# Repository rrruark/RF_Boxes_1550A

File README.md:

<p>Design files for a few electronics projects.</p>

<ul>
  <li>LNA Box: http://robruark.com/projects/RF/LNA/general_purpose_lna/general_lna.html</li>
  <li>Filter box: http://robruark.com/projects/RF/Filters/ham_filter_box/filter_box.html</li>
</ul>

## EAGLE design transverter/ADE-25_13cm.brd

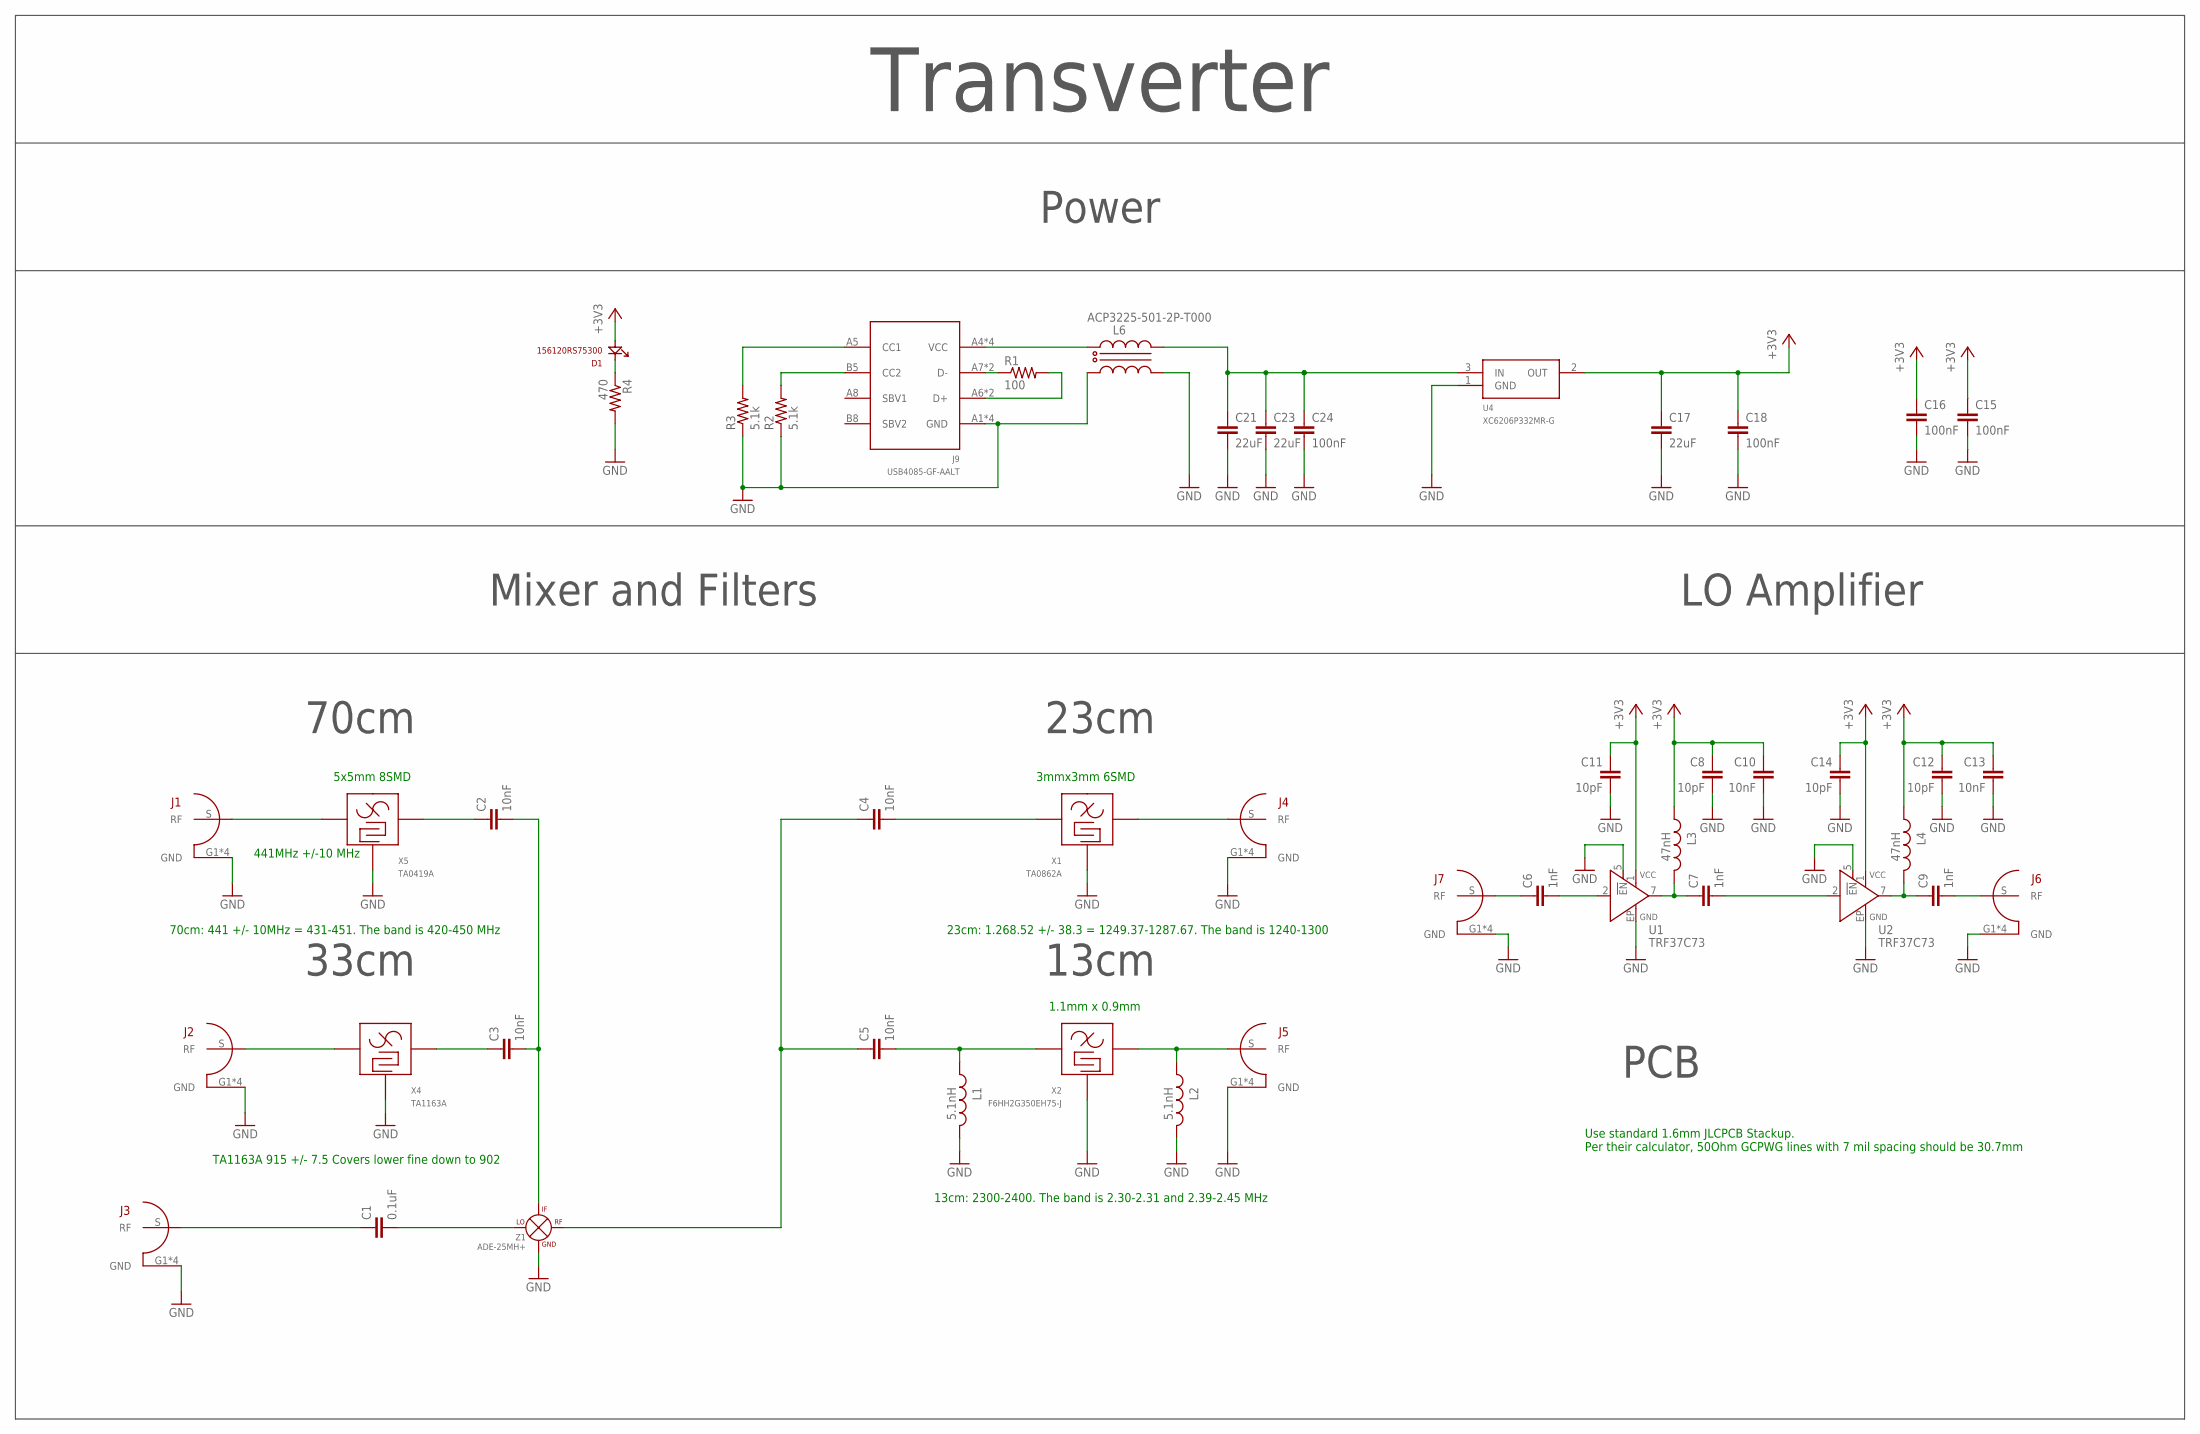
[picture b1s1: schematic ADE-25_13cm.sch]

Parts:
C1: 0.1uF; 0603
C2, C3, C4, C5: 10nF; 0603
C6, C7, C9: 1nF; 0603
C8, C11, C12, C14: 10pF; 0402_INDUCTOR
C10, C13: 10nF; 0402_INDUCTOR
C15, C16, C18, C24: 100nF; 0603
C17, C21, C23: 22uF; C1206
D1: 156120RS75300; 1206_REV
J1, J2, J3, J4, J5, J6, J7: 0733910070; CONREVSMA008-G
J9: USB4085-GF-AALT; USBC2
L1, L2: 5.1nH; 0402_INDUCTOR
L3, L4: 47nH; 0402_INDUCTOR
L6: ACP3225-501-2P-T000; 3225
R1: 100; 0603
R2, R3: 5.1k; 0603
R4: 470; 0603
U1, U2: TRF37C73; 8WSON2X2
U4: XC6206P332MR-G; SOT23-3_CENTERED
X1: TA0862A
X2: F6HH2G350EH75-J; EH75
X4: TA1163A; TA0862A
X5: TA0419A; TAO419
Z1: ADE-25MH+; CD

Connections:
1I: C4.2, X1.B
1O: J4.S (RF), X1.E
2I: C5.2, L1.P$1, X2.1
2O: J5.S (RF), L2.P$1, X2.4
70BI: C3.1, X4.B
70BO: J2.S (RF), X4.E
+3V3: C8.P$1 (1), C10.P$1 (1), C11.P$1 (1), C12.P$1 (1), C13.P$1 (1), C14.P$1 (1), C15.1, C16.1, C17.1, C18.1, D1.A, L3.P$1, L4.P$1, U1.1 (+VS), U2.1 (+VS), U4.2 (OUT)
+5V1: C21.1, C23.1, C24.1, L6.4 (1OUT), U4.3 (IN)
GND: C8.P$2 (2), C10.P$2 (2), C11.P$2 (2), C12.P$2 (2), C13.P$2 (2), C14.P$2 (2), C15.2, C16.2, C17.2, C18.2, C21.2, C23.2, C24.2, J1.G1 (GND), J1.G2 (GND), J1.G3 (GND), J1.G4 (GND), J2.G1 (GND), J2.G2 (GND), J2.G3 (GND), J2.G4 (GND), J3.G1 (GND), J3.G2 (GND), J3.G3 (GND), J3.G4 (GND), J4.G1 (GND), J4.G2 (GND), J4.G3 (GND), J4.G4 (GND), J5.G1 (GND), J5.G2 (GND), J5.G3 (GND), J5.G4 (GND), J6.G1 (GND), J6.G2 (GND), J6.G3 (GND), J6.G4 (GND), J7.G1 (GND), J7.G2 (GND), J7.G3 (GND), J7.G4 (GND), J9.A1 (GND), J9.A12 (GND), J9.B1 (GND), J9.B12 (GND), L1.P$2, L2.P$2, L6.2 (2IN), L6.3 (2OUT), R2.1, R3.1, R4.2, U1.5 (!EN), U1.EP (-VS), U2.5 (!EN), U2.EP (-VS), U4.1 (GND), X1.A (GND), X1.C (GND), X1.D (GND), X1.F (GND), X2.2 (GND), X2.3 (GND), X2.5 (GND), X4.A (GND), X4.C (GND), X4.D (GND), X4.F (GND), X5.1 (GND), X5.3 (GND), X5.4 (GND), X5.5 (GND), X5.7 (GND), X5.8 (GND), Z1.1 (GND), Z1.4 (GND), Z1.5 (GND)
IN1: C6.2, U1.2 (IN)
IN2: C7.2, U2.2 (IN)
unnamed: C1.1, J3.S (RF)
unnamed: C1.2, Z1.6 (LO)
unnamed: C2.1, X5.2
unnamed: C2.2, C3.2, Z1.2 (IF)
unnamed: C4.1, C5.1, Z1.3 (RF)
unnamed: J9.A7 (D-), J9.B7 (D-), R1.1
unnamed: J9.A6 (D+), J9.B6 (D+), R1.2
unnamed: J9.B5 (CC2), R2.2
unnamed: J9.A5 (CC1), R3.2
unnamed: D1.K, R4.1
unnamed: J9.A4 (VCC), J9.A9 (VCC), J9.B4 (VCC), J9.B9 (VCC), L6.1 (1IN)
unnamed: C6.1, J7.S (RF)
unnamed: C9.2, J6.S (RF)
unnamed: J1.S (RF), X5.6
OUT1: C7.1, L3.P$2, U1.7 (OUT)
OUT2: C9.1, L4.P$2, U2.7 (OUT)

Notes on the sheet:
441MHz +/-10 MHz
Use standard 1.6mm JLCPCB Stackup. Per their calculator, 50Ohm GCPWG lines with 7 mil spacing should be 30.7mm
1.1mm x 0.9mm
3mmx3mm 6SMD
5x5mm 8SMD
TA1163A 915 +/- 7.5 Covers lower fine down to 902
23cm: 1.268.52 +/- 38.3 = 1249.37-1287.67. The band is 1240-1300
70cm: 441 +/- 10MHz = 431-451. The band is 420-450 MHz
13cm: 2300-2400. The band is 2.30-2.31 and 2.39-2.45 MHz
Transverter
70cm
23cm
13cm
33cm
PCB
Power
Mixer and Filters
LO Amplifier

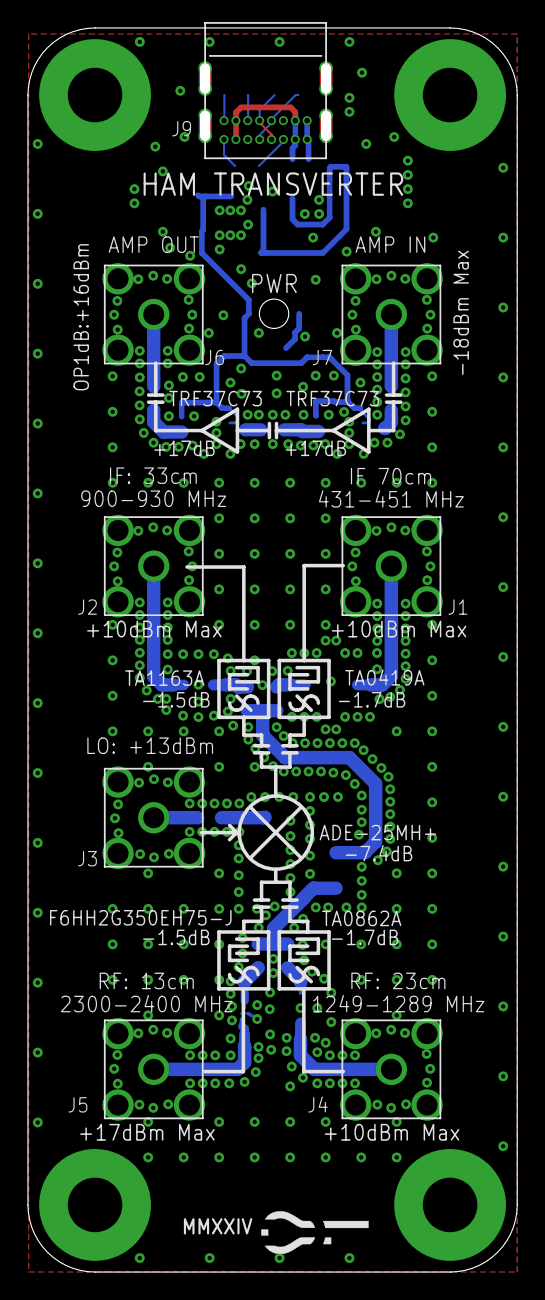
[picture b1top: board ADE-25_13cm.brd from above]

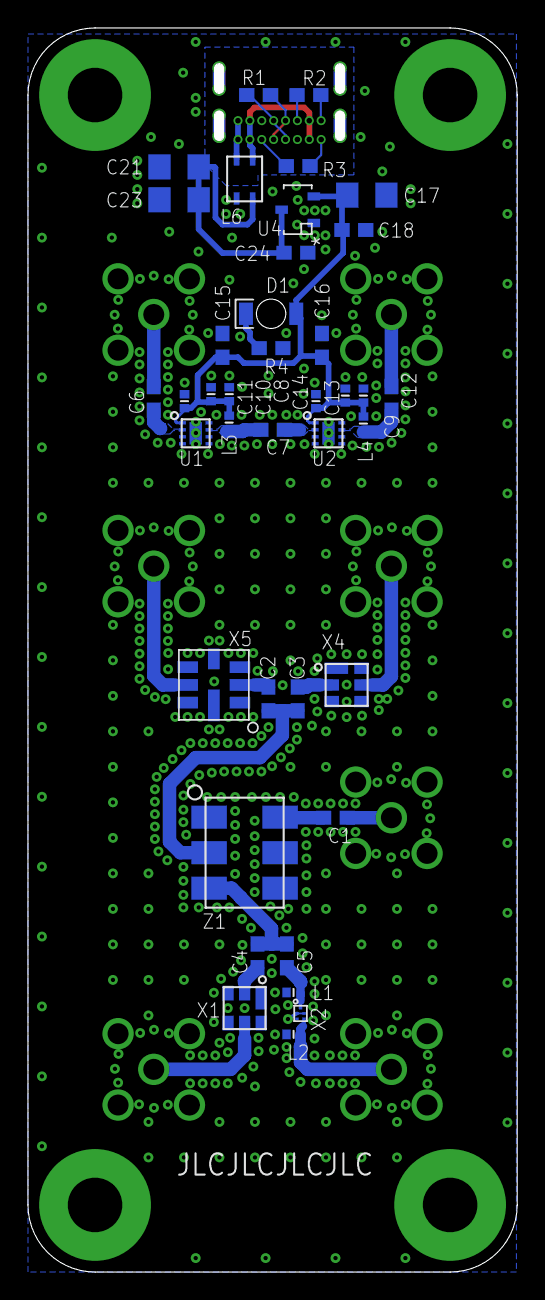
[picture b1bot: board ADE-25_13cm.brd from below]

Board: 2 copper layers, 34.3 x 88.3 mm, 47 parts (39 on the bottom side), 27 nets.

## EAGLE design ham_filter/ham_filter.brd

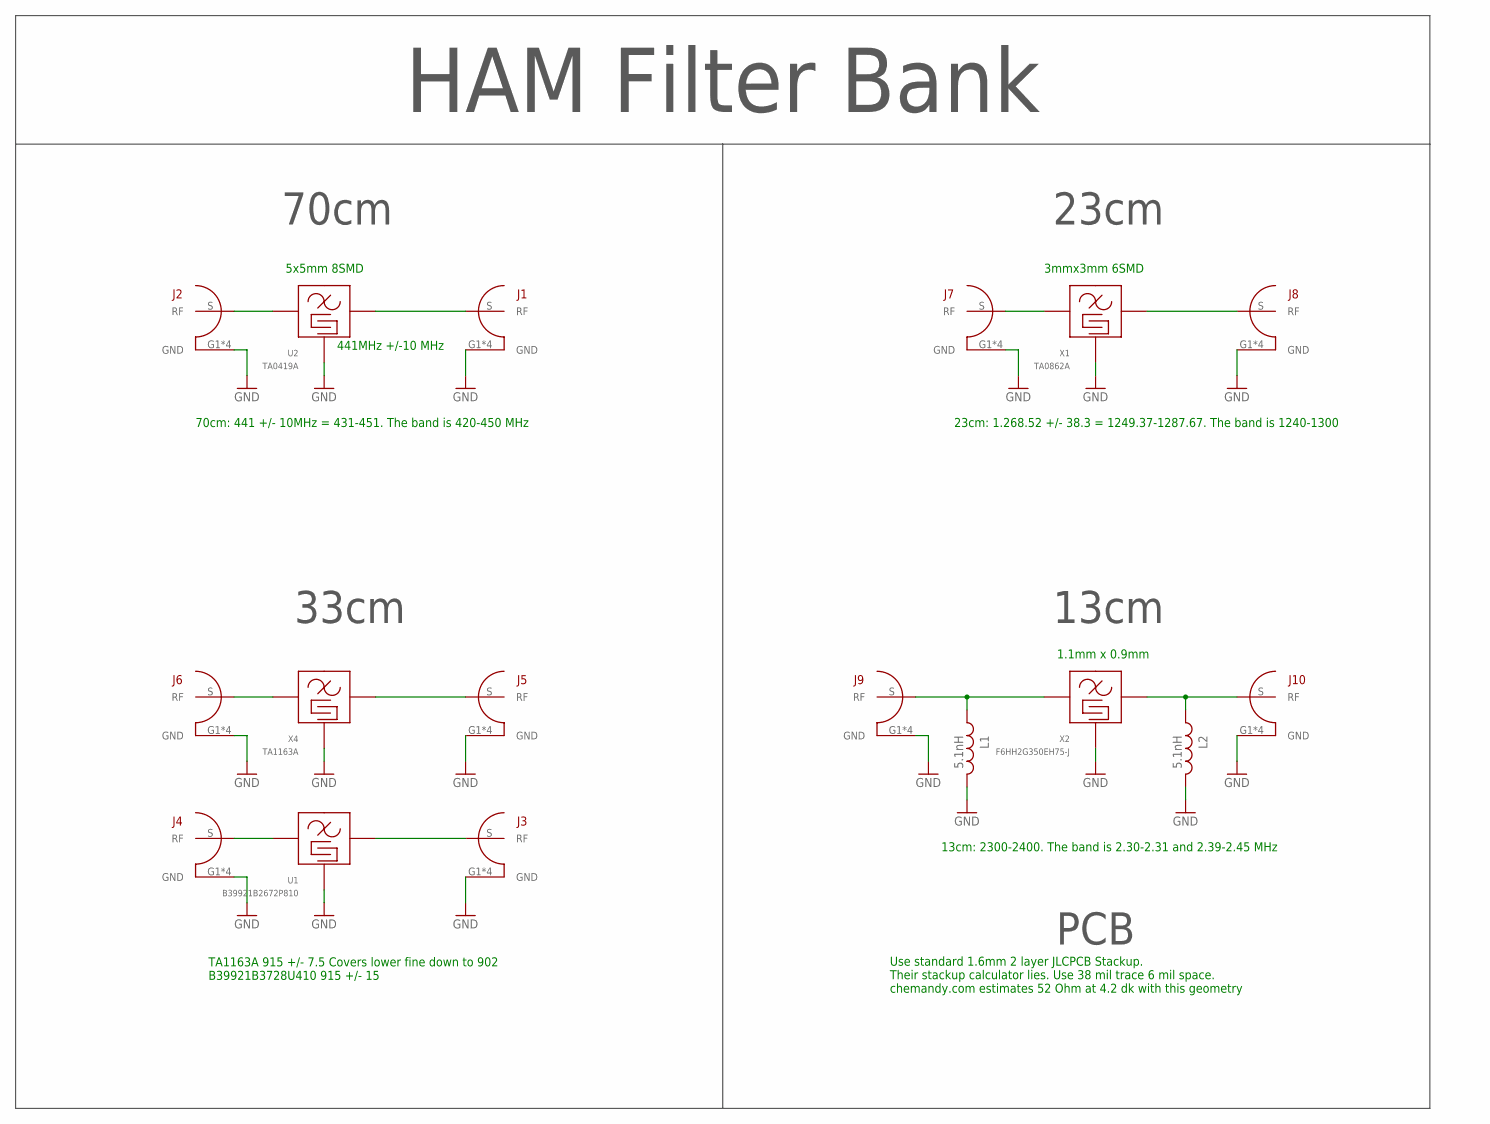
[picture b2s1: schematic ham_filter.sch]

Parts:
J1, J2, J3, J4, J5, J6, J7, J8, J9, J10: 0733910070; CONREVSMA008-G
L1, L2: 5.1nH; 0402_INDUCTOR
U1: B39921B2672P810; B2672
U2: TA0419A; TAO419
X1: TA0862A
X2: F6HH2G350EH75-J; EH75
X4: TA1163A; TA0862A

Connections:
1I: J7.S (RF), X1.B
1O: J8.S (RF), X1.E
2I: J9.S (RF), L1.P$1, X2.1
2O: J10.S (RF), L2.P$1, X2.4
70BI: J6.S (RF), X4.B
70BO: J5.S (RF), X4.E
GND: J1.G1 (GND), J1.G2 (GND), J1.G3 (GND), J1.G4 (GND), J2.G1 (GND), J2.G2 (GND), J2.G3 (GND), J2.G4 (GND), J3.G1 (GND), J3.G2 (GND), J3.G3 (GND), J3.G4 (GND), J4.G1 (GND), J4.G2 (GND), J4.G3 (GND), J4.G4 (GND), J5.G1 (GND), J5.G2 (GND), J5.G3 (GND), J5.G4 (GND), J6.G1 (GND), J6.G2 (GND), J6.G3 (GND), J6.G4 (GND), J7.G1 (GND), J7.G2 (GND), J7.G3 (GND), J7.G4 (GND), J8.G1 (GND), J8.G2 (GND), J8.G3 (GND), J8.G4 (GND), J9.G1 (GND), J9.G2 (GND), J9.G3 (GND), J9.G4 (GND), J10.G1 (GND), J10.G2 (GND), J10.G3 (GND), J10.G4 (GND), L1.P$2, L2.P$2, U1.2 (GND), U1.3 (GND), U1.5 (GND), U2.1 (GND), U2.3 (GND), U2.4 (GND), U2.5 (GND), U2.7 (GND), U2.8 (GND), X1.A (GND), X1.C (GND), X1.D (GND), X1.F (GND), X2.2 (GND), X2.3 (GND), X2.5 (GND), X4.A (GND), X4.C (GND), X4.D (GND), X4.F (GND)
unnamed: J2.S (RF), U2.2
unnamed: J3.S (RF), U1.4
unnamed: J4.S (RF), U1.1
unnamed: J1.S (RF), U2.6

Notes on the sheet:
441MHz +/-10 MHz
Use standard 1.6mm 2 layer JLCPCB Stackup. Their stackup calculator lies. Use 38 mil trace 6 mil space. chemandy.com estimates 52 Ohm at 4.2 dk with this geometry
1.1mm x 0.9mm
3mmx3mm 6SMD
5x5mm 8SMD
TA1163A 915 +/- 7.5 Covers lower fine down to 902 B39921B3728U410 915 +/- 15
23cm: 1.268.52 +/- 38.3 = 1249.37-1287.67. The band is 1240-1300
70cm: 441 +/- 10MHz = 431-451. The band is 420-450 MHz
13cm: 2300-2400. The band is 2.30-2.31 and 2.39-2.45 MHz
HAM Filter Bank
70cm
23cm
13cm
33cm
PCB

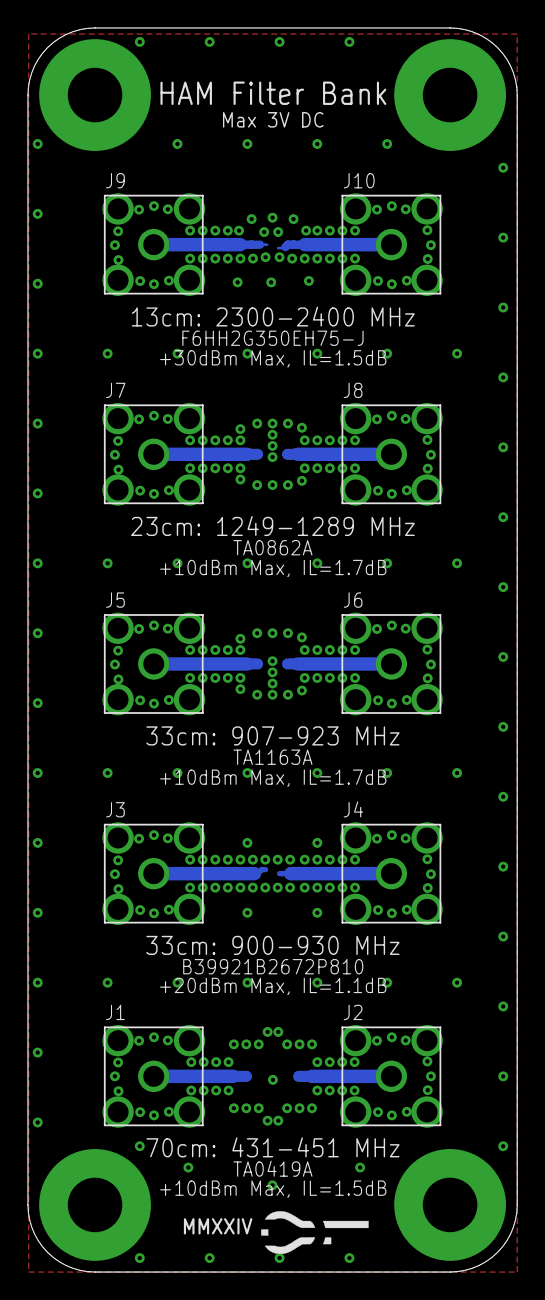
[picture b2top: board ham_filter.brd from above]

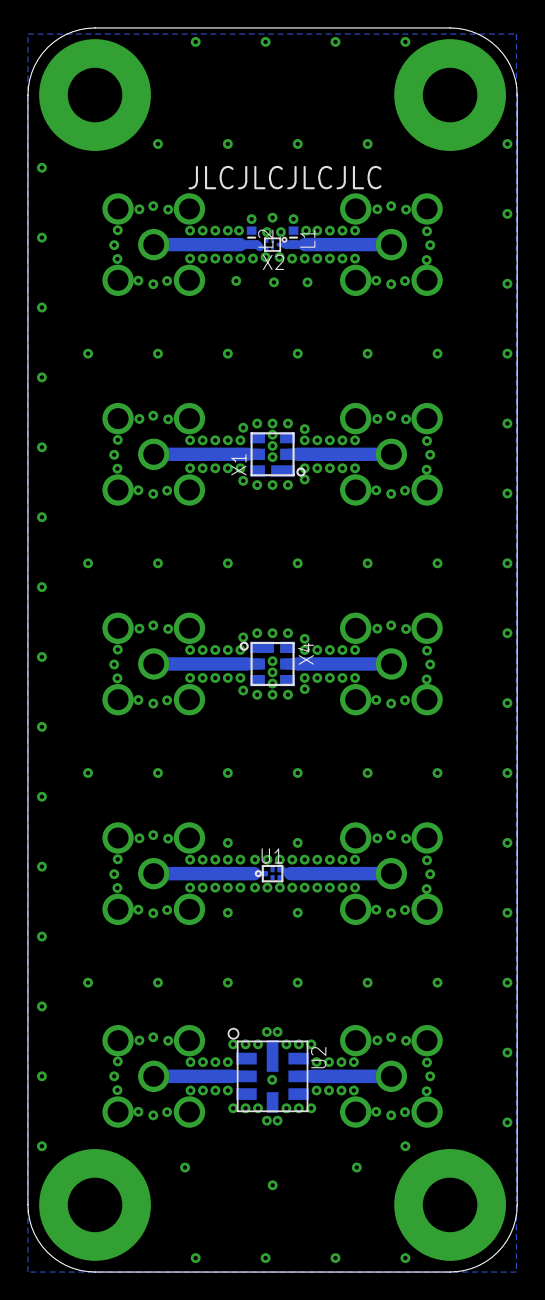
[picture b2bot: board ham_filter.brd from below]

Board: 2 copper layers, 35.0 x 89.0 mm, 17 parts (7 on the bottom side), 11 nets.

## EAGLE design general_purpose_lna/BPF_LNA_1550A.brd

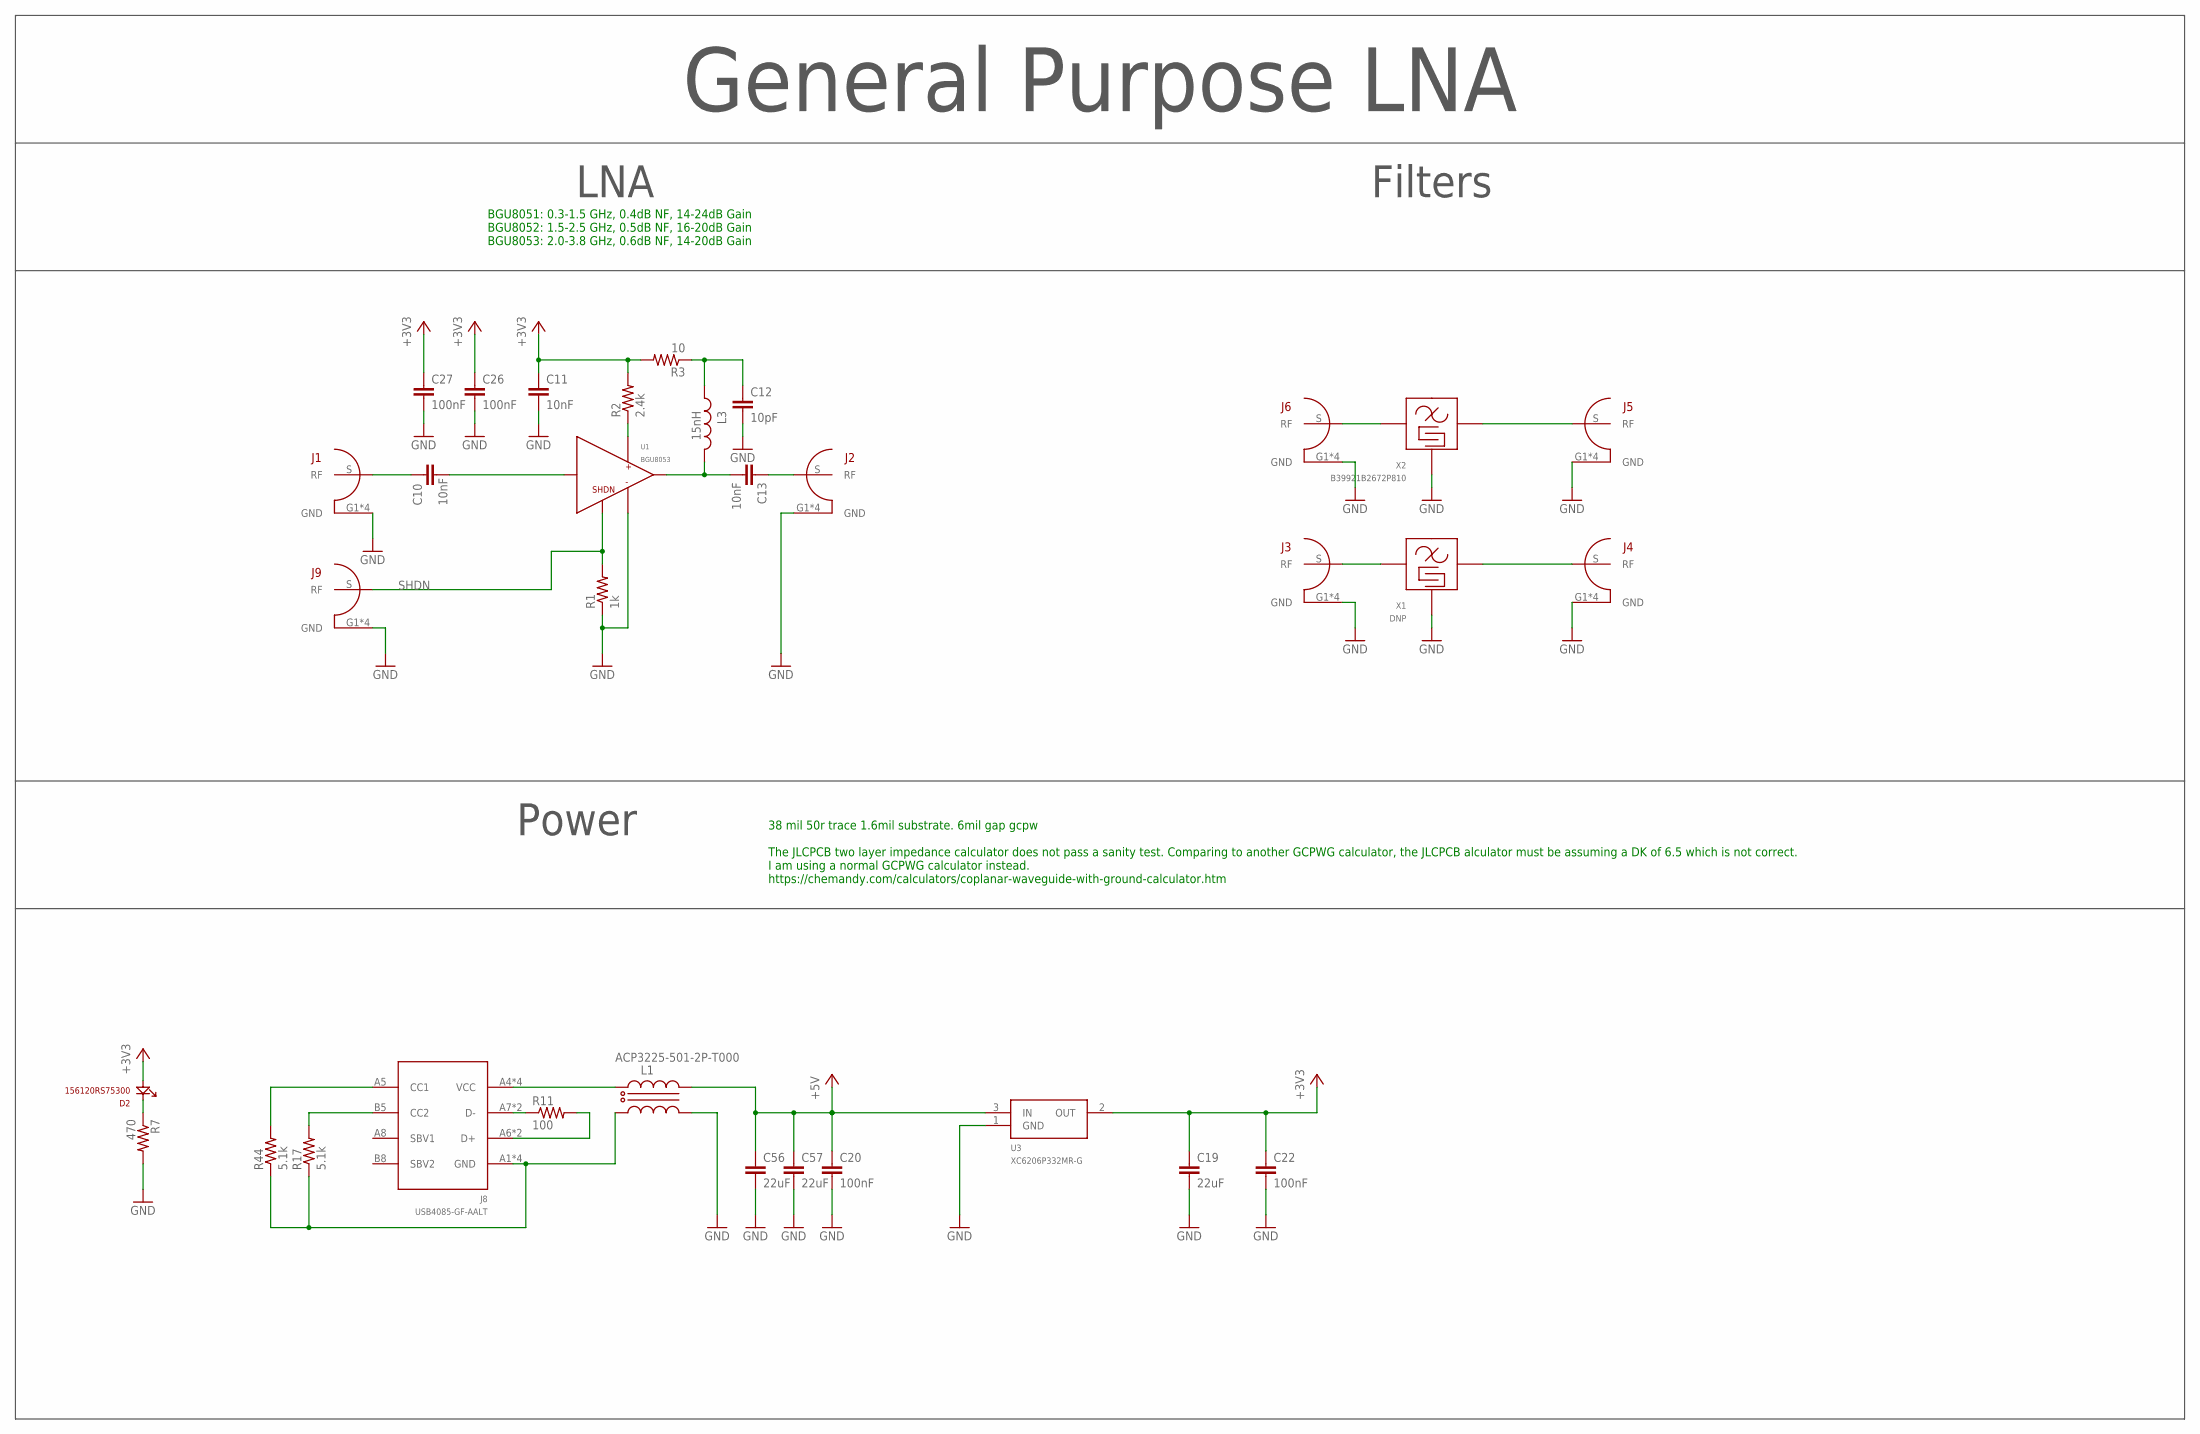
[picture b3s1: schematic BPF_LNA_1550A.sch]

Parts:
C10, C11, C13: 10nF; 0603
C12: 10pF; 0603
C19, C56, C57: 22uF; C1206
C20, C22, C26, C27: 100nF; 0603
D2: 156120RS75300; 1206_REV
J1, J2, J3, J4, J5, J6, J9: 0733910070; CONREVSMA008-G
J8: USB4085-GF-AALT; USBC2
L1: ACP3225-501-2P-T000; 3225
L3: 15nH; 0603
R1: 1k; 0603
R2: 2.4k; 0603
R3: 10; 0603
R7: 470; 0603
R11: 100; 0603
R17, R44: 5.1k; 0603
U1: BGU8053; SOT1327-1
U3: XC6206P332MR-G; SOT23-3_CENTERED
X1: DNP; TA0862A
X2: B39921B2672P810; B2672

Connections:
+3V3: C11.1, C19.1, C22.1, C26.1, C27.1, D2.A, R2.2, R3.2, U3.2 (OUT)
+5V: C20.1, C56.1, C57.1, L1.4 (1OUT), U3.3 (IN)
AMPIN: C10.2, U1.2 (IN)
AMP_OUT: C13.2, L3.2, U1.7 (OUT)
GND: C11.2, C12.2, C19.2, C20.2, C22.2, C26.2, C27.2, C56.2, C57.2, J1.G1 (GND), J1.G2 (GND), J1.G3 (GND), J1.G4 (GND), J2.G1 (GND), J2.G2 (GND), J2.G3 (GND), J2.G4 (GND), J3.G1 (GND), J3.G2 (GND), J3.G3 (GND), J3.G4 (GND), J4.G1 (GND), J4.G2 (GND), J4.G3 (GND), J4.G4 (GND), J5.G1 (GND), J5.G2 (GND), J5.G3 (GND), J5.G4 (GND), J6.G1 (GND), J6.G2 (GND), J6.G3 (GND), J6.G4 (GND), J9.G1 (GND), J9.G2 (GND), J9.G3 (GND), J9.G4 (GND), L1.3 (2OUT), R1.1, R7.2, U1.EP (GND), U3.1 (GND), X1.A (GND), X1.C (GND), X1.D (GND), X1.F (GND), X2.2 (GND), X2.3 (GND), X2.5 (GND)
unnamed: D2.K, R7.1
unnamed: J3.S (RF), X1.B
unnamed: J5.S (RF), X2.4
unnamed: C10.1, J1.S (RF)
unnamed: J8.A1 (GND), J8.A12 (GND), J8.B1 (GND), J8.B12 (GND), L1.2 (2IN), R17.1, R44.1
unnamed: J6.S (RF), X2.1
unnamed: R2.1, U1.1 (VCC)
unnamed: J8.A4 (VCC), J8.A9 (VCC), J8.B4 (VCC), J8.B9 (VCC), L1.1 (1IN)
unnamed: C12.1, L3.1, R3.1
unnamed: C13.1, J2.S (RF)
unnamed: J4.S (RF), X1.E
unnamed: J8.A7 (D-), J8.B7 (D-), R11.1
unnamed: J8.A6 (D+), J8.B6 (D+), R11.2
unnamed: J8.B5 (CC2), R17.2
unnamed: J8.A5 (CC1), R44.2
SHDN: J9.S (RF), R1.2, U1.6 (SHDN)

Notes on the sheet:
38 mil 50r trace 1.6mil substrate. 6mil gap gcpw The JLCPCB two layer impedance calculator does not pass a sanity test. Comparing to another GCPWG calculator, the JLCPCB alculator must be assuming a DK of 6.5 which is not correct. I am using a normal GCPWG calculator instead. https://chemandy.com/c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
BGU8051: 0.3-1.5 GHz, 0.4dB NF, 14-24dB Gain BGU8052: 1.5-2.5 GHz, 0.5dB NF, 16-20dB Gain BGU8053: 2.0-3.8 GHz, 0.6dB NF, 14-20dB Gain
General Purpose LNA
Filters
LNA
Power

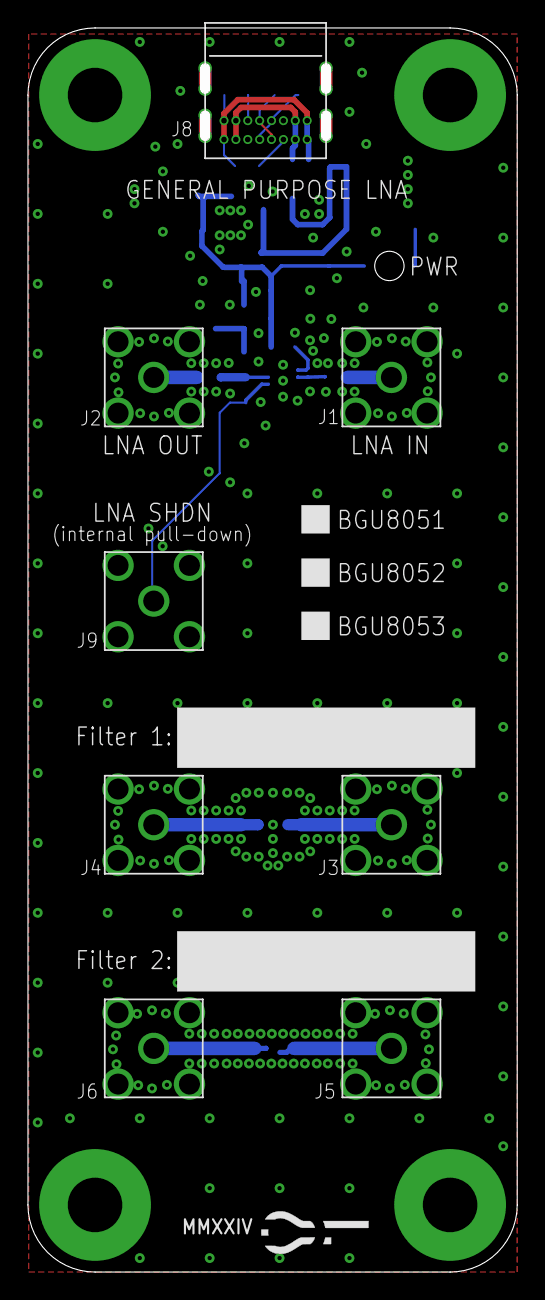
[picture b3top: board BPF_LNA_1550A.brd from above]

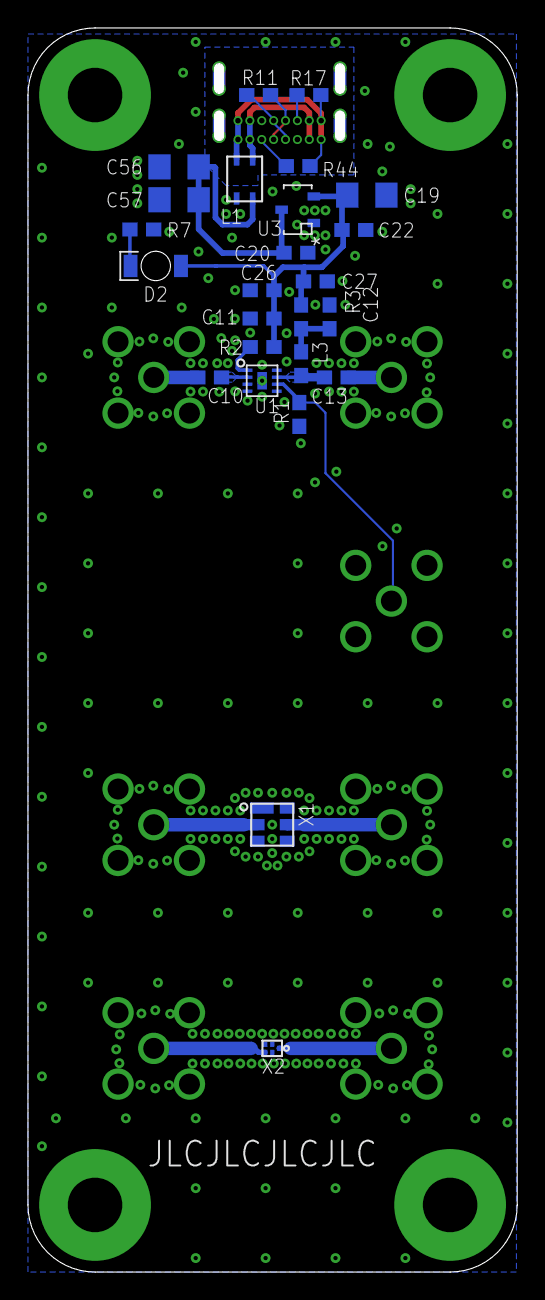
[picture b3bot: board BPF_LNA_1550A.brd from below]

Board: 2 copper layers, 34.3 x 88.3 mm, 33 parts (25 on the bottom side), 21 nets.

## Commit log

2025-02-02 doc updates
2025-02-02 Adding pdf schematics
